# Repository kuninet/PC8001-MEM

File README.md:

# PC-8001 32k x4バンク拡張メモリーボード

## 概要
- PC-8001のN-BASIC ROM/空きROM領域(アドレス0000h～7FFFh)の裏側に4バンクのメモリーを増設するボードです。
- バンク切り替えはPC-8012/8801などと同様の操作にしています。

## 拡張メモリー切り替え
- I/Oアドレス E2 : 
  - bit0 (01h)
    - 0 : N-BASIC ROM READ
    - 1 : 拡張RAM READ
  - bit4 (10h)
    - 1 : 拡張RAM WRITE
- I/Oアドレス E3 : 
  - メモリーバンク番号を0～4で指定します。リセット時デフォルトは0です。 
  - 128kB SRAMを4分割(4バンク)切り替えを実施して使用できます。
  - 0000h～7FFFhまでが切り替わるため、N-BASIC ROMは見えなくなります。(バンク切り替えし、書き込みのみ許可しておいて 切り替えることは可能)

## ライセンス
- 本リポジトリのファイルはMITライセンスで公開します。

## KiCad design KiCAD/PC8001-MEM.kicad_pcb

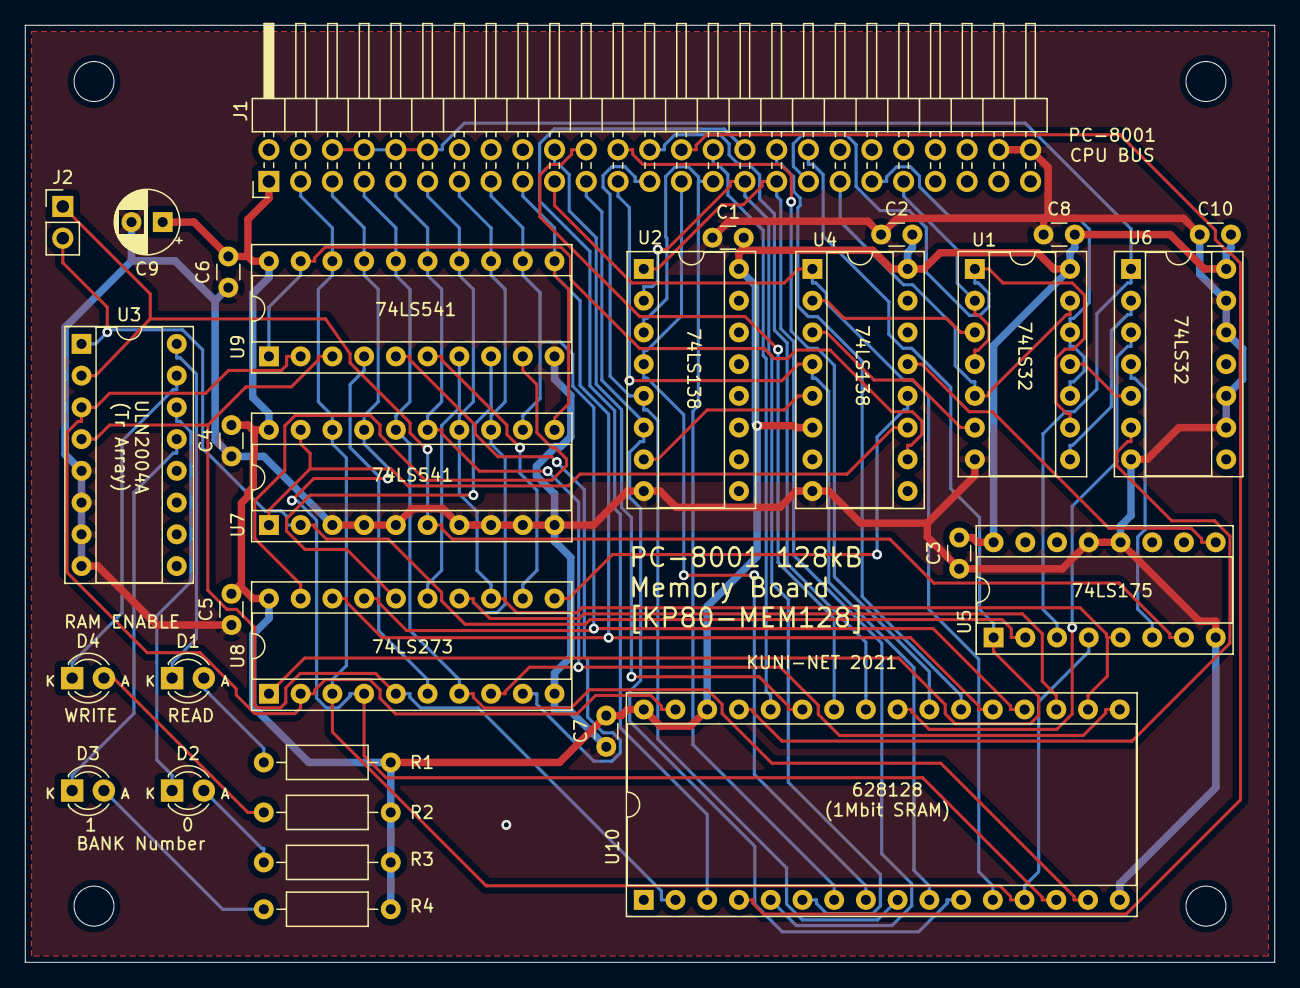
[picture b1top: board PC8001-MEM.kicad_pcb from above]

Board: 2 copper layers, 100.0 x 75.0 mm, 34 parts (0 on the bottom side), 62 nets.

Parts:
C1, C2, C3, C4, C5, C6, C7, C8, C10: 0.1u; C_Disc_D3.0mm_W1.6mm_P2.50mm
C9: 10u; CP_Radial_D5.0mm_P2.50mm
D1: LED_D0; LED_D3.0mm
D2: LED_ID0; LED_D3.0mm
D3: LED_ID1; LED_D3.0mm
D4: LED_D4; LED_D3.0mm
J1: PC-8001 ext BUS; PinHeader_2x25_P2.54mm_Horizontal
J2: MEM-CON; PinHeader_1x02_P2.54mm_Vertical
MH1, MH2, MH3, MH4: MountingHole; MountingHole_3.2mm_M3
R1, R2, R3, R4: 1k; R_Axial_DIN0207_L6.3mm_D2.5mm_P10.16mm_Horizontal
U1, U6: 74LS32; DIP-14_W7.62mm_Socket
U2, U4: 74LS138; DIP-16_W7.62mm_Socket
U3: ULN2003A; DIP-16_W7.62mm_Socket
U5: 74LS175; DIP-16_W7.62mm_Socket
U7, U9: 74LS541; DIP-20_W7.62mm_Socket
U8: 74LS273; DIP-20_W7.62mm_Socket
U10: 628128; DIP-32_W15.24mm_Socket

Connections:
/A0: J1.19, U4.1, U10.12
/A1: J1.21, U2.6, U10.11
/A2: J1.23, U4.4, U10.10
/A3: J1.25, U2.5, U10.9
/A4: J1.27, U2.4, U10.8
/A5: J1.29, U2.3, U10.7
/A6: J1.31, U2.2, U10.6
/A7: J1.33, U2.1, U10.5
/A8: J1.20, U10.27
/A9: J1.22, U10.26
/A10: J1.24, U10.23
/A11: J1.26, U10.25
/A12: J1.28, U10.4
/A13: J1.30, U10.28
/A14: J1.32, U10.3
/A15: J1.34, U10.22
/D0: J1.3, U5.4, U7.18, U8.3, U9.18, U10.13
/D1: J1.5, U7.17, U8.4, U9.17, U10.14
/D2: J1.7, U7.16, U8.7, U9.16, U10.15
/D3: J1.9, U7.15, U8.8, U9.15, U10.17
/D4: J1.11, U5.5, U7.14, U8.13, U9.14, U10.18
/D5: J1.13, U7.13, U8.14, U9.13, U10.19
/D6: J1.15, U7.12, U8.17, U9.12, U10.20
/D7: J1.17, U7.11, U8.18, U9.11, U10.21
/E2#RD: U4.11, U7.1, U7.19
/E2#WR: U4.13, U5.9
/E2-D0: J2.2, U3.1, U5.2, U7.2
/E2-D4: J2.1, U3.2, U5.7, U7.6
/E3#RD: U4.10, U9.1, U9.19
/E3#WR: U4.12, U8.11
/ID0: U3.3, U8.2, U9.2, U10.31
/ID1: U3.4, U8.5, U9.3, U10.2
/ID2: U8.6, U9.4
/ID3: U8.9, U9.5
/ID4: U8.12, U9.6
/ID5: U8.15, U9.7
/ID6: U8.16, U9.8
/ID7: U8.19, U9.9
/~IORD: U1.3, U4.2
/~IOREQ: J1.41, U1.2, U1.4
/~IOWR: U1.6, U4.3
/~MRD: U1.8, U6.2
/~MREQ: J1.39, U1.10, U1.12
/~MWR: U1.11, U6.5
/~RAMRD: U6.3, U10.24
/~RAMWR: U6.6, U10.29
/~RD: J1.35, U1.1, U1.9
/~RESET: J1.36, U5.1, U8.1
/~ROMDS0: J1.6, J1.8, J1.10, J1.12, U5.3, U6.1
/~WR: J1.37, U1.5, U1.13
GND: C1.1, C2.1, C3.1, C4.1, C5.1, C6.1, C7.1, C8.1, C9.2, C10.1, J1.48, J1.50, U1.7, U2.8, U3.5, U3.6, U3.7, U3.8, U4.8, U5.8, U5.12, U5.13, U6.7, U6.9, U6.10, U6.12, U6.13, U7.3, U7.4, U7.5, U7.7, U7.8, U7.9, U7.10, U8.10, U9.10, U10.16
unnamed: D1.1, U3.16
unnamed: D1.2, R1.2
unnamed: D2.1, U3.14
unnamed: D2.2, R3.2
unnamed: D3.1, U3.13
unnamed: D3.2, R4.2
unnamed: D4.1, U3.15
unnamed: D4.2, R2.2
unnamed: U2.7, U4.5
unnamed: U5.6, U6.4
VCC: C1.2, C2.2, C3.2, C4.2, C5.2, C6.2, C7.2, C8.2, C9.1, C10.2, J1.1, R1.1, R2.1, R3.1, R4.1, U1.14, U2.16, U4.6, U4.16, U5.16, U6.14, U7.20, U8.20, U9.20, U10.30, U10.32

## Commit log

2021-01-11 init
2021-01-11 README追加
2021-01-11 README.md 名前間違い訂正
2021-01-11 Create LICENSE
2021-01-11 回路図修正、イメージ追加
2021-01-11 アドレス E2用 LED追加
2021-01-11 回路修正(ROM KILL間違い)
2021-01-13 E2hのレジスタを74LS175へ変更、LEDドライバ変更
2021-01-13 回路図イメージ差し替え
2021-01-17 N-BASIC COPYデモ
2021-01-17 LS273、LS175のCp信号の部分の間違い訂正
2021-01-17 回路図差し替え
2021-01-21 Revert "回路図差し替え"
    This reverts commit 483a819fbeebb61eaf4f5652be9b0b19720a5eab.
2021-01-21 Revert "LS273、LS175のCp信号の部分の間違い訂正"
    This reverts commit dc92f6c23538d2a9134d8bc83470156b4a3e76cd.
2021-02-07 プリント基板化検討
2021-02-07 パターン更新
2021-02-18 ガーバーデータ出力
2021-03-12 8k SRAMボードコントロール信号端子追加・ガーバーデータ再出力
2021-03-12 回路図変更
